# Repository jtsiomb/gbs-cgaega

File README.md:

GBS-8200 CGA/EGA input board
============================

The GBS-8200 video upscaler is advertised as being able to convert CGA/EGA video
to VGA, but it can't handle either without further modification. The missing
pieces for being able to feed CGA and EGA video to the GBS board are the
following:

  - The GBS board accepts analog RGB video signals from 0V to 1V, while CGA and
    EGA video signals are digital with TTL logic levels.
  - The GBS board can only use combined H+V sync, while CGA and EGA have
    separate horizontal and vertical sync signals.
  - EGA modes use a 21KHz horizontal scan rate, which the GBS board does not
    accept.

This project only tackles the first two items on the list, which are sufficient
for successfully converting CGA to VGA with the GBS-8200. If you wish to make
the GBS-8200 accept EGA frequencies, you will need something like this:
https://github.com/ramapcsx2/gbs-control in conjunction with this input board.

License
-------
Copyright (C) 2021 John Tsiombikas <nuclear@member.fsf.org>

The CGA/EGA input board is a free hardware design. Feel free to use, modify,
and/or redistribute it under the terms of the GNU General Public License v3, or
at your option any later version published by the Free Software Foundation. See
LICENSE for details.

Theory of operation
-------------------
Schematic: http://nuclear.mutantstargoat.com/hw/gbs-cgaega/gbs-cgaega-schem.pdf

The CGA/EGA input board is a small daughterboard, which plugs directly over the
8-pin video input connector of the GBS-8200, and is powered by the GBS board
through the 2-pin power connector at the top-right of the board.

The CGA/EGA input board is comprised of a cheap programmable logic chip
(GAL16V8), and a simple resistor network for digital to analog conversion.

The GAL chip is programmed with the logic equations in `cgaega.pld` to:

  - Combine the H and V sync signals to combined H+V sync.
  - Convert the CGA (RGB + intensity) TTL signals, to EGA-compatible (RrGgBb)
    TTL signals.
  - Detect the CGA dark yellow, and correct it to brown.

The last two items are only enabled when the CGA/EGA switch is set to CGA input.

Bill of Materials
-----------------

  - 1x GAL16V8 programmable logic chip.
  - 1x IC socket for the GAL (10pin DIP).
  - 1x Female pin header connector 1x8 pins, 2.54mm pitch.
  - 1x JST 2.54mm pitch male pin header (optional).
  - 3x 470 ohm resistors SMD 0805.
  - 3x 680 ohm resistors SMD 0805.
  - 1x 4.7k ohm resistor SMD 0805.
  - 1x 0.1uF capacitor SMD 0805.
  - 2x through hole 3-pin SPDT PCB-mounted mini switches 2.54mm pitch.
    Alternatively 3-pin single row pin headers can be used with jumpers.
  - 1x D-SUB 9-pin female connector, PCB-mounted.

You will also need an appropriate D-SUB 9-pin cable (male to male)
to connect the CGA/EGA video card to the input board. A straight through (not
null-modem) serial cable can be used, but make sure it's fully wired; some
serial cables carry only the Rx/Tx signals and ground, and are not suitable.

For the power lead, you can solder the 2-pin power cable which comes with the
GBS-8200 board directly to the input board and plug it into the GBS power
connector. Alternatively you can install a JST 2-pin connector on the input
board, and make an appropriate cable with JST female connectors on both ends.

Build instructions
------------------
To build a CGA/EGA input board:

  - zip the contents of the `gerber` directory and send it to a PCB fabrication
    service of your choice (popular choices are jlcpcb and pcbway).
  - Acquire the necessary components (see Bill of Materials section).
  - Assemble the board, and program the GAL chip with the included pre-compiled
    `cgaega.jed` file.

A cheap EEPROM programmer like the TL866 can be used to program the GAL.

If you wish to build the JED file from the `cgaega.pld` source, you'll need
GALasm (https://github.com/daveho/GALasm). Unfortunately GALasm is not free
software; if you can suggest a free software alternative, please let me know!
When you have everything set up, simply type `make`.

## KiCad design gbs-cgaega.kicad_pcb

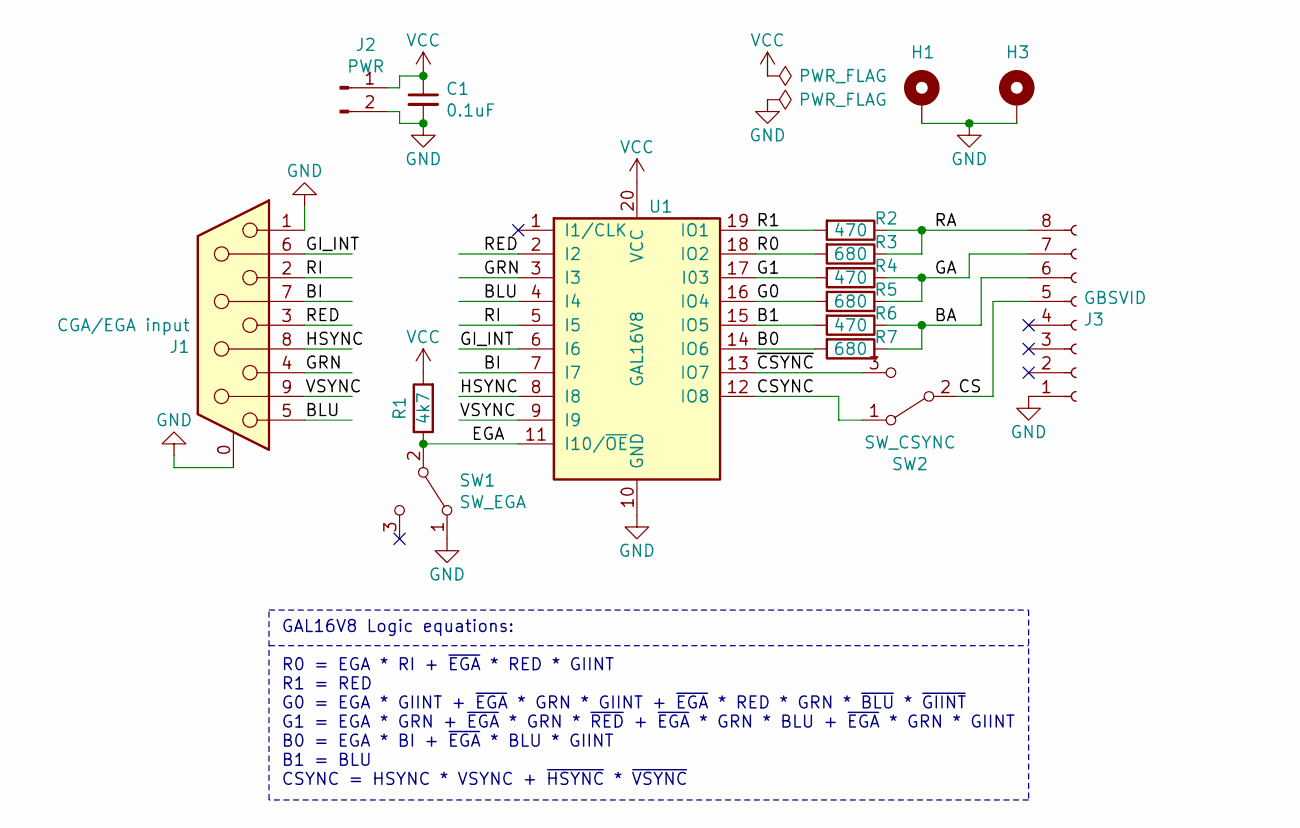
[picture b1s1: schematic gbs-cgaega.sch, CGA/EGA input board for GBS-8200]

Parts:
C1: 0.1uF; C_0805_2012Metric_Pad1.15x1.40mm_HandSolder
H1, H3: mhole; MountingHole_3.2mm_M3_ISO7380_Pad
J1: CGA/EGA input; DSUB-9_Female_Horizontal_P2.77x2.84mm_EdgePinOffset7.70mm_H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
J2: PWR; JST_EH_B2B-EH-A_1x02_P2.50mm_Vertical
J3: GBSVID; JST_EH_B8B-EH-A_1x08_P2.50mm_Vertical
R1: 4k7; R_0805_2012Metric_Pad1.15x1.40mm_HandSolder
R2, R4, R6: 470; R_0805_2012Metric_Pad1.15x1.40mm_HandSolder
R3, R5, R7: 680; R_0805_2012Metric_Pad1.15x1.40mm_HandSolder
SW1: SW_EGA; PinHeader_1x03_P2.54mm_Vertical
SW2: SW_CSYNC; PinHeader_1x03_P2.54mm_Vertical
U1: GAL16V8; DIP-20_W7.62mm_Socket_LongPads

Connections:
/B0: R7.2, U1.14 (IO6)
/B1: R6.2, U1.15 (IO5)
/BA: J3.6, R6.1, R7.1
/BI: J1.7, U1.7 (I7)
/BLU: J1.5, U1.4 (I4)
/CS: J3.5, SW2.2 (B)
/CSYNC: SW2.1 (A), U1.12 (IO8)
/EGA: R1.1, SW1.2 (B), U1.11 (I10/~OE~)
/G0: R5.2, U1.16 (IO4)
/G1: R4.2, U1.17 (I03)
/GA: J3.7, R4.1, R5.1
/GI_INT: J1.6, U1.6 (I6)
/GRN: J1.4, U1.3 (I3)
/HSYNC: J1.8, U1.8 (I8)
/R0: R3.2, U1.18 (IO2)
/R1: R2.2, U1.19 (IO1)
/RA: J3.8, R2.1, R3.1
/RED: J1.3, U1.2 (I2)
/RI: J1.2, U1.5 (I5)
/VSYNC: J1.9, U1.9 (I9)
/~CSYNC: SW2.3 (C), U1.13 (IO7)
GND: C1.2, H1.1, H3.1, J1.0 (PAD), J1.1, J2.2, J3.1, SW1.1 (A), U1.10 (GND)
VCC: C1.1, J2.1, R1.2, U1.20 (VCC)

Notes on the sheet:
GAL16V8 Logic equations: R0 = EGA * RI + ~EGA~ * RED * GIINT R1 = RED G0 = EGA * GIINT + ~EGA~ * GRN * GIINT + ~EGA~ * RED * GRN * ~BLU~ * ~GIINT~ G1 = EGA * GRN + ~EGA~ * GRN * ~RED~ + ~EGA~ * GRN * BLU + ~EGA~ * GRN * GIINT B0 = EGA * BI + ~EGA~ * BLU * GIINT B1 = BLU CSYNC = HSYNC * VSYNC + ~HSY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

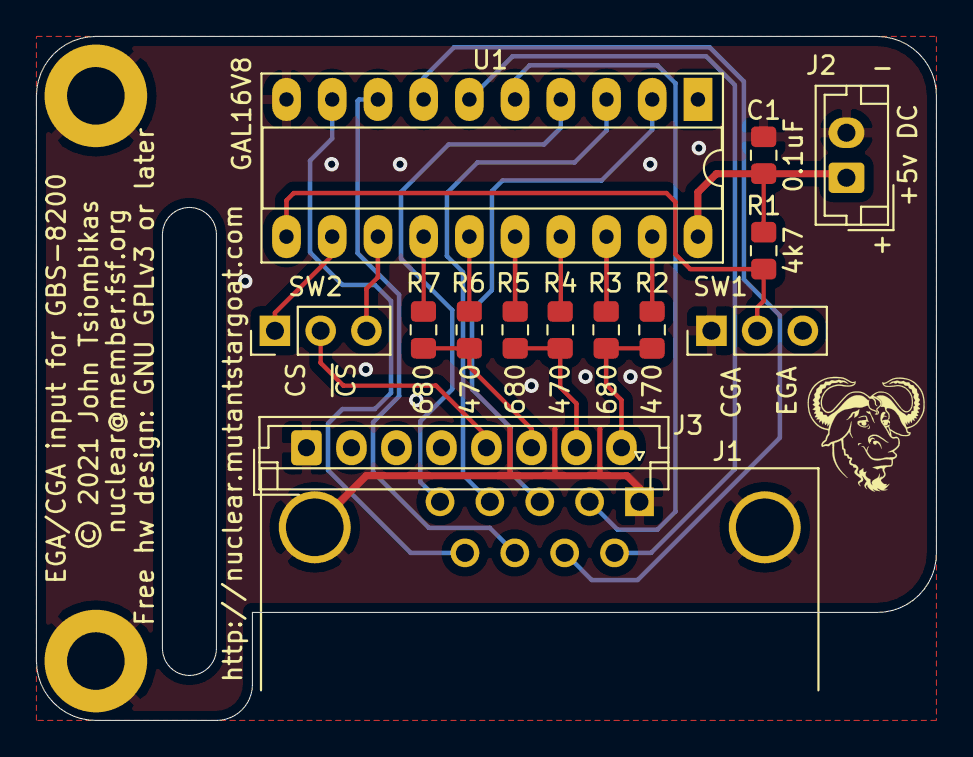
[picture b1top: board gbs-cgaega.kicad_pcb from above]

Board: 2 copper layers, 50.0 x 38.0 mm, 16 parts (0 on the bottom side), 23 nets.

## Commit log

2021-07-28 added photo link to the readme file

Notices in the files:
gbs-cgaega.kicad_pcb:
Free hw design: GNU GPLv3 or later
© 2021 John Tsiombikas
gbs-cgaega.sch:
License: GNU General Public License v3 or later
Copyright © John Tsiombikas <nuclear@member.fsf.org
